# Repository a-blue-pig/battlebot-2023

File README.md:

# battlebot-2023
BattleBot Project for ME366J

Course Completed in FALL 2023.

## Project Materials
### Microcontroller
Project uses an Arduino Nano Every as the microcontroller.
Requires the following packages/board packages:
1. Servo.
2. Arduino megaAVR Boards.

### Drivetrain
Differential Drive with 2 Motors.
Motor Controller is an L298N.

### Weapon
Weapon is a vertical spinner, made of Aluminum.
It is powered by a 30A ESC with a 2212 2200Kv Motor on a pulley with a 
2.3:1 gear ratio to add torque.

### Controller
Uses a generic RC car controller with 4 Channels.

### Power
Powered using a 3S 1300mAh Lipo.

## Usage/Controls
* The speed channel controls forward and backward movement.
* The steering channel allows for pivoting in place.
    * When combined with speed, it drives like a normal car.
* Channel 3 activates/deactivates the weapon.
* Channel 4 is a software E-Stop.

## Notes about the project
In this project we utilized various engineering practices to create a
battle bot from scratch. Our budget was $300 and we were given ~ 4 weeks
to procure and build our battlebot.

Based on the component we bought we realized our selection of RC
controller had a lot of noise and would not always send signals when
channel 3 and 4 were pressed. As a result I had to get creative in how to
determine if the signal was a true on or true off for the weapon activatiaon.

Overall this project was a strong learning experience and allowed me to
try out kiCAD when drawing our schematics and designing a custom PCB.
The PCB was ultimately made by hand using a protoboard and wires, but was
a unique experience.

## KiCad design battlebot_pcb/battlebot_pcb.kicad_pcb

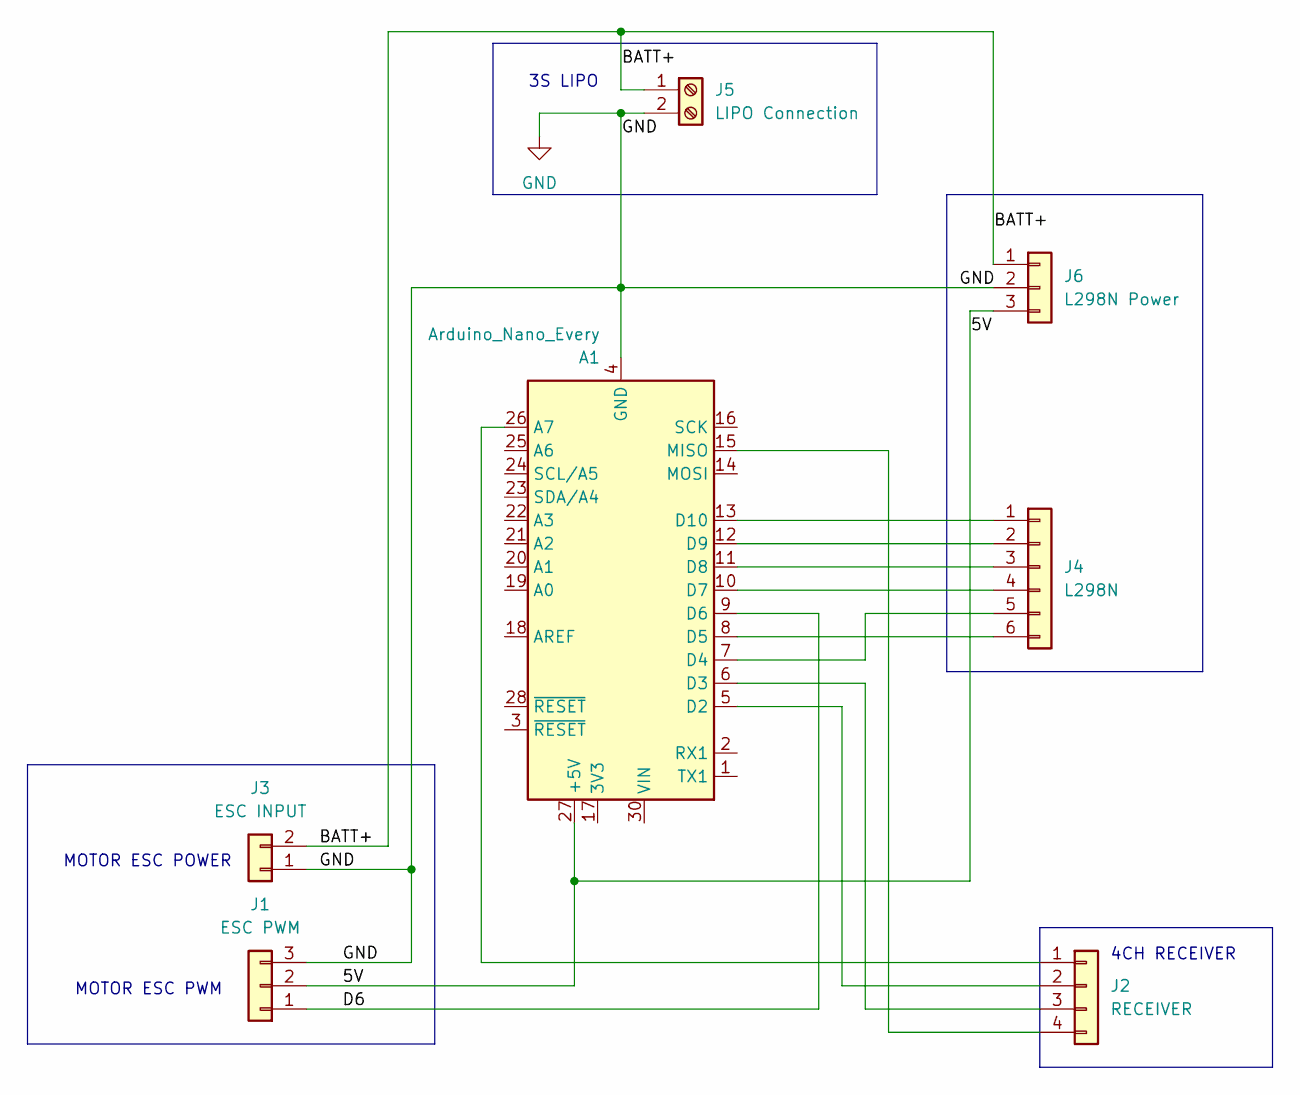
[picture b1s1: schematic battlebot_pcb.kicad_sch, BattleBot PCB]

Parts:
A1: Arduino_Nano_Every; Arduino_Nano
J1: ESC PWM; PinSocket_1x03_P2.54mm_Vertical
J2: RECEIVER; PinSocket_1x04_P2.54mm_Vertical
J3: ESC INPUT; TerminalBlock_TE_282834-2_1x02_P2.54mm_Horizontal
J4: L298N; PinSocket_1x06_P2.54mm_Vertical
J5: LIPO Connection; TerminalBlock_TE_282834-2_1x02_P2.54mm_Horizontal
J6: L298N Power; SolderWire-0.75sqmm_1x03_P4.8mm_D1.25mm_OD2.3mm

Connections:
/5V: A1.27 (+5V), J1.2, J6.3
/BATT+: J3.2, J5.1, J6.1
/D6: A1.9 (D6), J1.1
GND: A1.4 (GND), A1.29 (GND), J1.3, J3.1, J5.2, J6.2
unnamed: A1.26 (A7), J2.1
unnamed: A1.5 (D2), J2.2
unnamed: A1.6 (D3), J2.3
unnamed: A1.7 (D4), J4.5
unnamed: A1.8 (D5), J4.6
unnamed: A1.10 (D7), J4.4
unnamed: A1.11 (D8), J4.3
unnamed: A1.12 (D9), J4.2
unnamed: A1.13 (D10), J4.1
unnamed: A1.15 (MISO), J2.4

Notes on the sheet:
MOTOR ESC POWER
4CH RECEIVER
MOTOR ESC PWM
3S LIPO

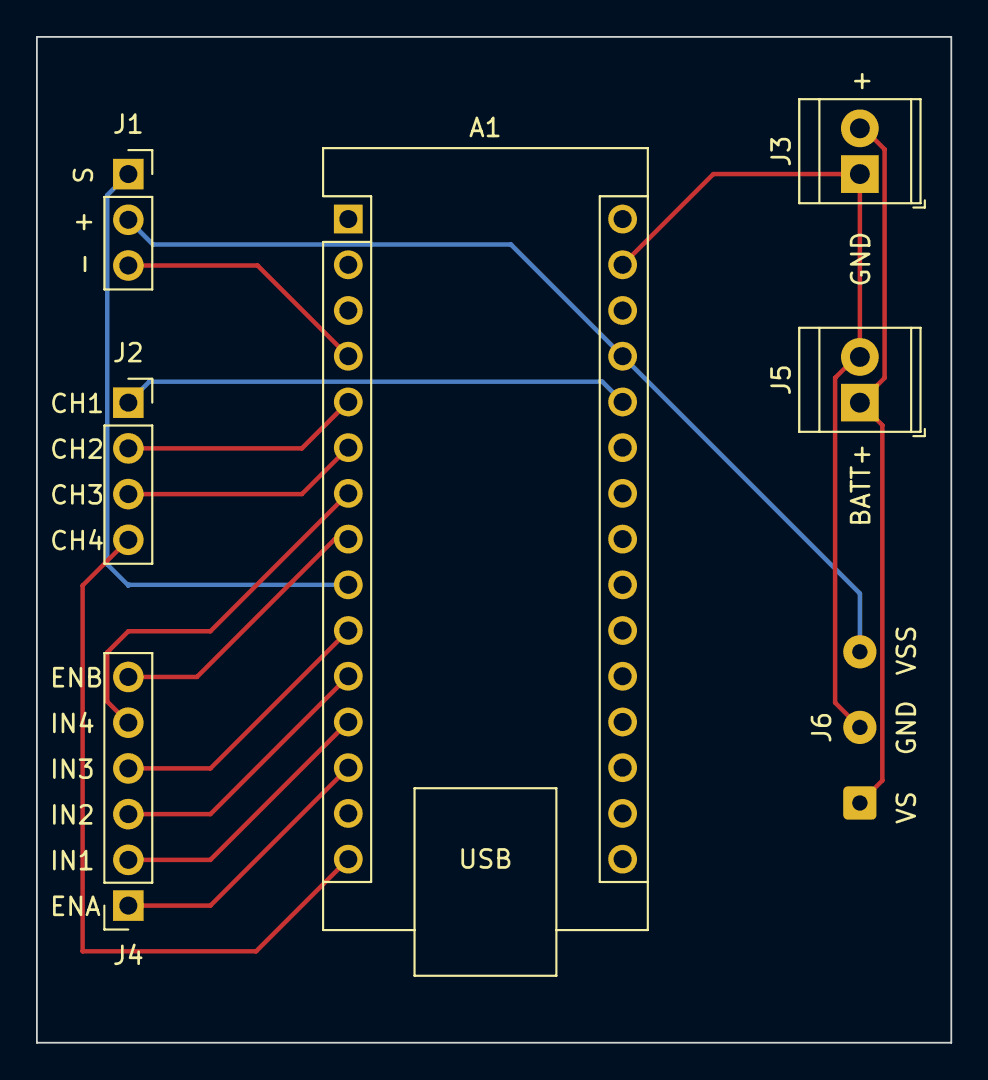
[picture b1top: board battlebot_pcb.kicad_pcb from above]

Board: 2 copper layers, 50.8 x 55.9 mm, 7 parts (0 on the bottom side), 14 nets.

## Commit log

2023-12-05 Adding BattleBot Arduino code, PCB/schematic projects
2023-12-05 circuit schematic and pcb outline
2023-12-05 updated electrical diagrams
2023-12-05 Added weapon pulsing, fixed weaponlow bug, reorg reference
2023-12-05 adding arduino pinout
2023-12-05 added pdf of schematic and pcb layout
2023-12-05 Closes #5; Motor ramps up before going to desired speed
2023-12-05 Fixed weapon pulsing, Fixed motor orientation issue.
2023-12-05 rename battlebot_pcb, update dates and revisions on sheets
2023-12-05 Added option to turn off pulsing
2023-12-05 Updated CH4 pin; increased the weaponLow value; Still working on unexpected weapon pulsing.
2023-12-05 cleaning up transition to own repo
